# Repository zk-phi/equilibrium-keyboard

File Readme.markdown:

# Equilibrium Keyboard

コンパクトで透明感を強調したデザインの一体型 40% キーボードです。バックライトを点灯するとケース全体が光ります。

一般にコンパクトとされるキーボードと比較してもかなりコンパクトなデザインになっています。

足プレートを組み合わせることで、 Cherry Profile のキーキャップなどと相性のいい 5 度の傾斜をつけることができます。

また内部の空洞を極力減らした設計により、音の響く空間が小さく、また重さも見た目以上にしっかりあるので、アクリルケースにしては音・打鍵感が良いです。硬さは一般的なサンドイッチ構造の自作キーボードと、金属プレートなどのしっかりした高級キーボードの中間くらいかなと思っています。個人的にはリニアスイッチと合わせて使っています。

一般的なキーボードのホームポジションが左寄りにある (右手小指の担当するキーが多い) のに対し、このキーボードは最上段を除いて左右対称の配置となっており、均整のとれたデザインになっています。減った分のキーは自作キーボードらしくスペースバーを割ることで補っています。最上段は一般的なキーボードと同じずれ方を再現するため左上にずれており、ノートパソコンなどの一般的なキーボードとの使い分けコストと、自作ならではの美しいレイアウトのバランスを意識した設計です。

また 2u 以上の長さのキーを使用せずに設計しているため、嫌な音の原因になりやすいスタビライザーが登場せず、パーツ選定で考えることがひとつ少なくなっています。

組み立てやすさよりも自己満足を優先して設計したので、初心者向けの自作キーボードと比較するとやや難しいです。またキーキャップも一般的なキャップセットだけだと必要なキーが揃わない可能性が高く、工夫する必要があります。２台目以降におすすめです。

# 必要なもの

キット
- 基板
- トップフレーム 2mm x 2, 3mm x 1
- トッププレート上 (3mm)
- トッププレート下 (2mm)
- ミドルプレート (2mm)
- ボトムプレート上 (3mm)
- ボトムプレート下 (3mm)
- 足プレート 三種類

予備部品
- トップフレーム 3mm x 1
- ボトムプレート上 2mm x 1

汎用部品
- キースイッチ, キーキャップ, ダイオード 1N4148w x41
- LED SK6812mini x67
- 2pin タクトスイッチ x1
- Pro Micro + コンスルー
- M2 ねじ 20mm (21mm) x13, 10mm x3, 8mm x3, 6mm x3
- M2 ナット x22
- 2mm 厚以上のゴムクッション x6 以上

# 組み立て
## ProMicro の準備
### ProMicro にファームウェアを書き込んでおく

ProMicro にあらかじめファームウェアを書き込んでおきます。

https://github.com/zk-phi/keyboard-buildguide-common/blob/master/firmware.markdown

[こちら](https://github.com/zk-phi/qmk_firmware) に私の使っているキーマップがアップロードされています。

```terminal
make equilibrium:phi:avrdude
```

### ProMicro にコンスルーを実装しておく

ProMicro を基板に連結するためのコンスルーを実装します。

https://github.com/zk-phi/keyboard-buildguide-common/blob/master/conthrough.markdown

このキーボードでは ProMicro を「部品面が内側になるように」使用します。

このキットはコンスルーの足 (ハンダ側) を切るかどうかで組み立て方が若干変わり、最終的なキーボードの厚みが 1mm 変わります。

私はコンスルーの足を切って 1mm 薄く組んでいますが、コンスルーの足を切って使って問題ないのかちゃんと調べていないので、心配な方は足を切らずに組んでください。

## 基板に各パーツを実装
### ダイオードを実装

ダイオードを実装します。

https://github.com/zk-phi/keyboard-buildguide-common/blob/master/diode.markdown

表面実装部品は、ガイドの印から大きくはみ出して取り付けてしまうと「ボトムプレート上」と干渉してケースが組めなくなってしまいますので、なるべく丁寧に位置を合わせてください。

### LED を実装 (オプション)

LED を実装します。

https://github.com/zk-phi/keyboard-buildguide-common/blob/master/neopixel.markdown

LED の実装順は Pro Micro 側上段のバックライト (背面実装・赤) からスタートして Z 字に降りていき、下段まで行ったらアンダーグロー (表面実装・青) で折り返すように進みます。

Pro Micro はコンスルー対応なので、逐次動作確認しながら進めていくのがオススメです。

### スイッチを実装

最後にスイッチを実装します。

このキーボードではトッププレートを２枚使用します。基板、トッププレート下、トッププレート上をこの順に重ねて、スイッチで挟み込んでください。

基板とプレート、プレートとスイッチの間が浮かないように注意、しっかりスイッチを押し付けてください (0.4mm 以上浮いていると基板が「ボトムプレート上」に干渉する可能性があります)。

２枚のトッププレートの間は全てのスイッチを外さない限りもう触れなくなるので、間にホコリなどを入れないように注意しながら重ねましょう。

プレートを清掃するときはメガネ拭きやグラス拭きなどがおすすめです。ティッシュだと繊維が散らかります。また **アルコールティッシュを清掃に使わないように注意してください** 。プレートはアクリル製なので最悪ヒビが入ったりします。

## (オプション) ボトムプレート下に足プレートを取り付け

角度を付けたい場合は、「ボトムプレート下」に足プレート３枚を、大きい順に取り付けます。

コスト削減の都合、アクリルは厚みに若干の個体差があります。キットに付属するネジはポリカネジ (予定) なので、ネジの長さがが余った場合はニッパなどで簡単に切ることができます。ゴム足をつけてもネジが机に当たってしまう場合は試してみてください。

## ケースを組立て

ボトムプレート下、ボトムプレート上、ミドルプレート、実装済みの基板、適当な枚数のトップフレームを重ねてねじ止め

「ボトムプレート上」には 3mm, 2mm の二種類があります。コンスルーの足を切らずに組みたい場合は 3mm を、少しでも薄くしたい場合はコンスルーの足 (ハンダ側) を切って 2mm を選んでください。

トップフレームは見た目と打鍵音のためについているだけなので、好みや手持ちのネジの長さに応じて調整可能です。デフォルトでは 2mm x 2 + 3mm x 1 の３枚を想定していますが、好みの厚み、枚数を選んでください。

表面にくるプレート以外は分解しないと触れなくなっていまうので、極力汚さないようにしましょう。

- キーキャップはめてゴム足つければ完成

図ではゴム足が４つ付いていますが、実際に組んでみたところ４つだとアクリルがしなってしまったので６つ以上つけるのがおすすめです。

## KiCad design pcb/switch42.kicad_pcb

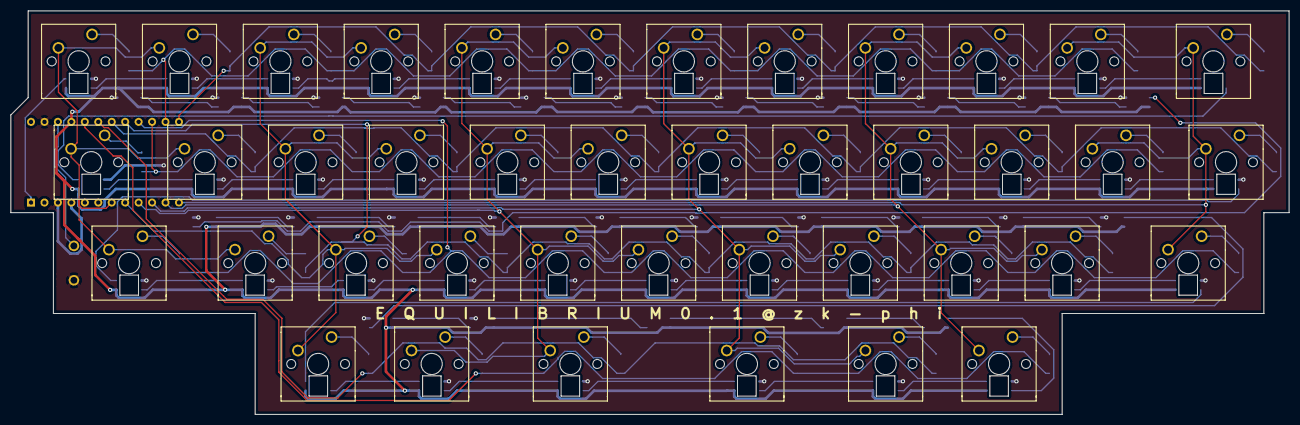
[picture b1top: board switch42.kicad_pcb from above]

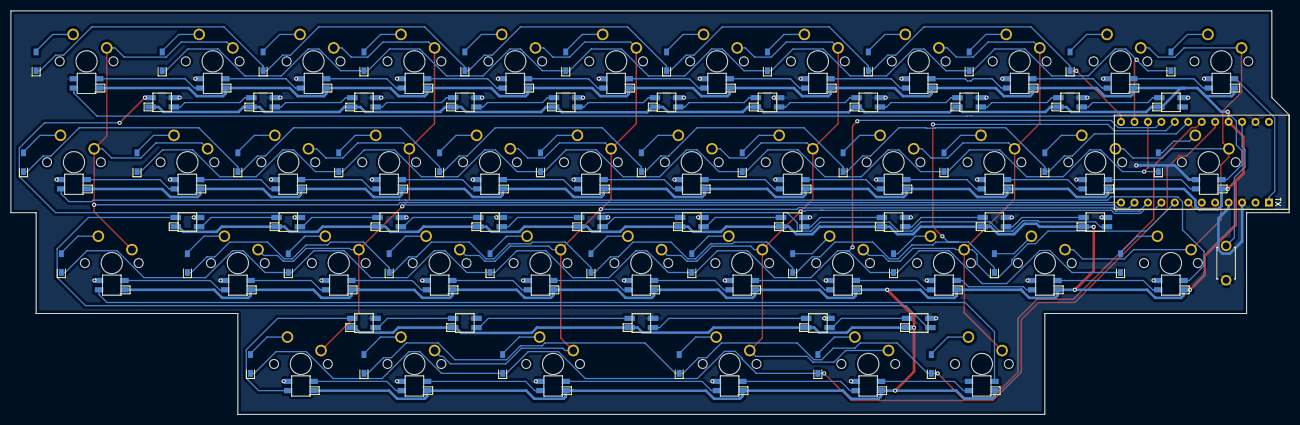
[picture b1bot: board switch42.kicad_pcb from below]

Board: 2 copper layers, 241.4 x 76.2 mm, 151 parts (69 on the bottom side), 125 nets.

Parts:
D1, D2, D3, D4, D5, D6, D7, D8, D9, D10, D11, D12, D13, D14, D15, D16, D17, D18, D19, D20, D21, D22, D23, D24, D25, D26, D27, D28, D29, D30, D31, D32, D33, D34, D35, D36, D37, D38, D39, D40, D41: D; D_SMD-irreversible
L1, L2, L3, L4, L5, L6, L10, L14, L18, L23, L28, L33, L54, L55, L56, L57, L58, L59, L60, L61, L62, L63, L64, L65, L66, L67: SK6812MINI; SK6812MINI-underglow-irreversible
L7, L8, L9, L11, L12, L13, L15, L16, L17, L19, L20, L21, L22, L24, L25, L26, L27, L29, L30, L31, L32, L34, L35, L36, L37, L38, L39, L40, L41, L42, L43, L44, L45, L46, L47, L48, L49, L50, L51, L52, L53: SK6812MINI; SK6812MINI_narrow-irreversible
SW1, SW4, SW5, SW6, SW7, SW8, SW9, SW11, SW12, SW13, SW15, SW16, SW17, SW18, SW19, SW20, SW21, SW23, SW24, SW25, SW27, SW28, SW29, SW30, SW31, SW32, SW33, SW35, SW36, SW37, SW38, SW39: SW_PUSH; MX_1.00u-irreversible
SW2, SW14, SW34, SW42: SW_PUSH; MX_1.25u-irreversible
SW3, SW40, SW41: SW_PUSH; MX_1.50u-irreversible
SW10: SW_PUSH; ResetSW-irreversible
SW22, SW26: SW_PUSH; MX_1.75u-irreversible
U1: ProMicro; ProMicro_Reversed_Conthrough-irreversible

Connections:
GND: L1.2, L2.2, L3.2, L4.2, L5.2, L6.2, L7.2, L8.2, L9.2, L10.2, L11.2, L12.2, L13.2, L14.2, L15.2, L16.2, L17.2, L18.2, L19.2, L20.2, L21.2, L22.2, L23.2, L24.2, L25.2, L26.2, L27.2, L28.2, L29.2, L30.2, L31.2, L32.2, L33.2, L34.2, L35.2, L36.2, L37.2, L38.2, L39.2, L40.2, L41.2, L42.2, L43.2, L44.2, L45.2, L46.2, L47.2, L48.2, L49.2, L50.2, L51.2, L52.2, L53.2, L54.2, L55.2, L56.2, L57.2, L58.2, L59.2, L60.2, L61.2, L62.2, L63.2, L64.2, L65.2, L66.2, L67.2, SW10.2, U1.3, U1.4, U1.23
unnamed: D1.2, SW1.2
unnamed: D2.2, SW2.2
unnamed: D3.2, SW3.2
unnamed: D4.2, SW4.2
unnamed: D5.2, SW5.2
unnamed: D6.2, SW6.2
unnamed: D7.2, SW7.2
unnamed: D8.2, SW8.2
unnamed: D9.2, SW9.2
unnamed: D10.2, SW11.2
unnamed: D11.2, SW12.2
unnamed: D12.2, SW13.2
unnamed: D13.2, SW14.2
unnamed: D14.2, SW15.2
unnamed: D15.2, SW16.2
unnamed: D16.2, SW17.2
unnamed: D17.2, SW18.2
unnamed: D18.2, SW19.2
unnamed: D19.2, SW20.2
unnamed: D20.2, SW21.2
unnamed: D21.2, SW22.2
unnamed: D22.2, SW23.2
unnamed: D23.2, SW24.2
unnamed: D24.2, SW25.2
unnamed: D25.2, SW26.2
unnamed: D26.2, SW27.2
unnamed: D27.2, SW28.2
unnamed: D28.2, SW29.2
unnamed: D29.2, SW30.2
unnamed: D30.2, SW31.2
unnamed: D31.2, SW32.2
unnamed: D32.2, SW33.2
unnamed: D33.2, SW34.2
unnamed: D34.2, SW35.2
unnamed: D35.2, SW36.2
unnamed: D36.2, SW37.2
unnamed: D37.2, SW38.2
unnamed: D38.2, SW39.2
unnamed: D39.2, SW40.2
unnamed: D40.2, SW41.2
unnamed: D41.2, SW42.2
unnamed: L1.1, L2.3
unnamed: L1.3, L67.1
unnamed: L2.1, L3.3
unnamed: L3.1, L4.3
unnamed: L4.1, L5.3
unnamed: L5.1, L6.3
unnamed: L10.1, L14.3
unnamed: L6.1, L10.3
unnamed: L11.1, L15.3
unnamed: L7.1, L11.3
unnamed: L12.1, L16.3
unnamed: L8.1, L12.3
unnamed: L13.1, L17.3
unnamed: L9.1, L13.3
unnamed: L14.1, L18.3
unnamed: L15.1, L19.3
unnamed: L16.1, L20.3
unnamed: L17.1, L21.3
unnamed: L18.1, L23.3
unnamed: L19.1, L24.3
unnamed: L20.1, L25.3
unnamed: L21.1, L26.3
unnamed: L22.1, L27.3
unnamed: L22.3, L51.1
unnamed: L23.1, L28.3
unnamed: L24.1, L29.3
unnamed: L25.1, L30.3
unnamed: L26.1, L31.3
unnamed: L27.1, L32.3
unnamed: L28.1, L33.3
unnamed: L29.1, L34.3
unnamed: L30.1, L35.3
unnamed: L31.1, L36.3
unnamed: L32.1, L37.3
unnamed: L33.1, L54.3
unnamed: L34.1, L38.3
unnamed: L35.1, L39.3
unnamed: L36.1, L40.3
unnamed: L37.1, L41.3
unnamed: L38.1, L42.3
unnamed: L39.1, L43.3
unnamed: L40.1, L44.3
unnamed: L41.1, L45.3
unnamed: L42.1, L46.3
unnamed: L43.1, L47.3
unnamed: L44.1, L48.3
unnamed: L46.1, L49.3
unnamed: L47.1, L50.3
unnamed: L48.1, L51.3
unnamed: L49.1, L52.3
unnamed: L50.1, L53.3
unnamed: L8.3, L52.1
unnamed: L9.3, L53.1
unnamed: L54.1, L55.3
unnamed: L55.1, L56.3
unnamed: L56.1, L57.3
unnamed: L57.1, L58.3
unnamed: L58.1, L59.3
unnamed: L59.1, L60.3
unnamed: L60.1, L61.3
unnamed: L61.1, L62.3
unnamed: L63.1, L64.3
unnamed: L64.1, L65.3
unnamed: L65.1, L66.3
unnamed: L66.1, L67.3
VCC: L1.4, L2.4, L3.4, L4.4, L5.4, L6.4, L7.4, L8.4, L9.4, L10.4, L11.4, L12.4, L13.4, L14.4, L15.4, L16.4, L17.4, L18.4, L19.4, L20.4, L21.4, L22.4, L23.4, L24.4, L25.4, L26.4, L27.4, L28.4, L29.4, L30.4, L31.4, L32.4, L33.4, L34.4, L35.4, L36.4, L37.4, L38.4, L39.4, L40.4, L41.4, L42.4, L43.4, L44.4, L45.4, L46.4, L47.4, L48.4, L49.4, L50.4, L51.4, L52.4, L53.4, L54.4, L55.4, L56.4, L57.4, L58.4, L59.4, L60.4, L61.4, L62.4, L63.4, L64.4, L65.4, L66.4, L67.4, U1.21
col01: SW1.1, SW2.1, SW3.1, SW4.1, SW5.1, SW6.1, U1.7
col23: SW7.1, SW8.1, SW9.1, SW11.1, SW12.1, SW13.1, SW14.1, U1.8
col45: SW15.1, SW16.1, SW17.1, SW18.1, SW19.1, SW20.1, SW21.1, SW22.1, U1.9
col67: SW23.1, SW24.1, SW25.1, SW26.1, SW27.1, SW28.1, SW29.1, SW30.1, U1.10
col89: SW31.1, SW32.1, SW33.1, SW34.1, SW35.1, SW36.1, SW37.1, U1.11
col1011: SW38.1, SW39.1, SW40.1, SW41.1, SW42.1, U1.12
led: L7.3, U1.1
reset: SW10.1, U1.22
row0a: D1.1, D7.1, D14.1, D22.1, D30.1, D37.1, U1.14
row0b: D4.1, D10.1, D18.1, D26.1, D34.1, D40.1, U1.13
row1a: D2.1, D8.1, D15.1, D23.1, D31.1, D38.1, U1.15
row1b: D5.1, D11.1, D19.1, D27.1, D35.1, D41.1, U1.18
row2a: D3.1, D9.1, D16.1, D24.1, D32.1, D39.1, U1.16
row2b: D6.1, D12.1, D20.1, D28.1, D36.1, U1.17
row3a: D17.1, D25.1, D33.1, U1.20
row3b: D13.1, D21.1, D29.1, U1.19
underglow: L45.1, L63.3

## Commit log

2020-03-23 Add Readme
2020-03-27 updat readme
2020-04-16 fix readme
2020-04-16 fix (again) readme
2020-05-08 replace image
2020-06-17 Add PCB
2020-06-17 Add License
2020-08-30 Update buildguide
2023-02-19 Replace img
